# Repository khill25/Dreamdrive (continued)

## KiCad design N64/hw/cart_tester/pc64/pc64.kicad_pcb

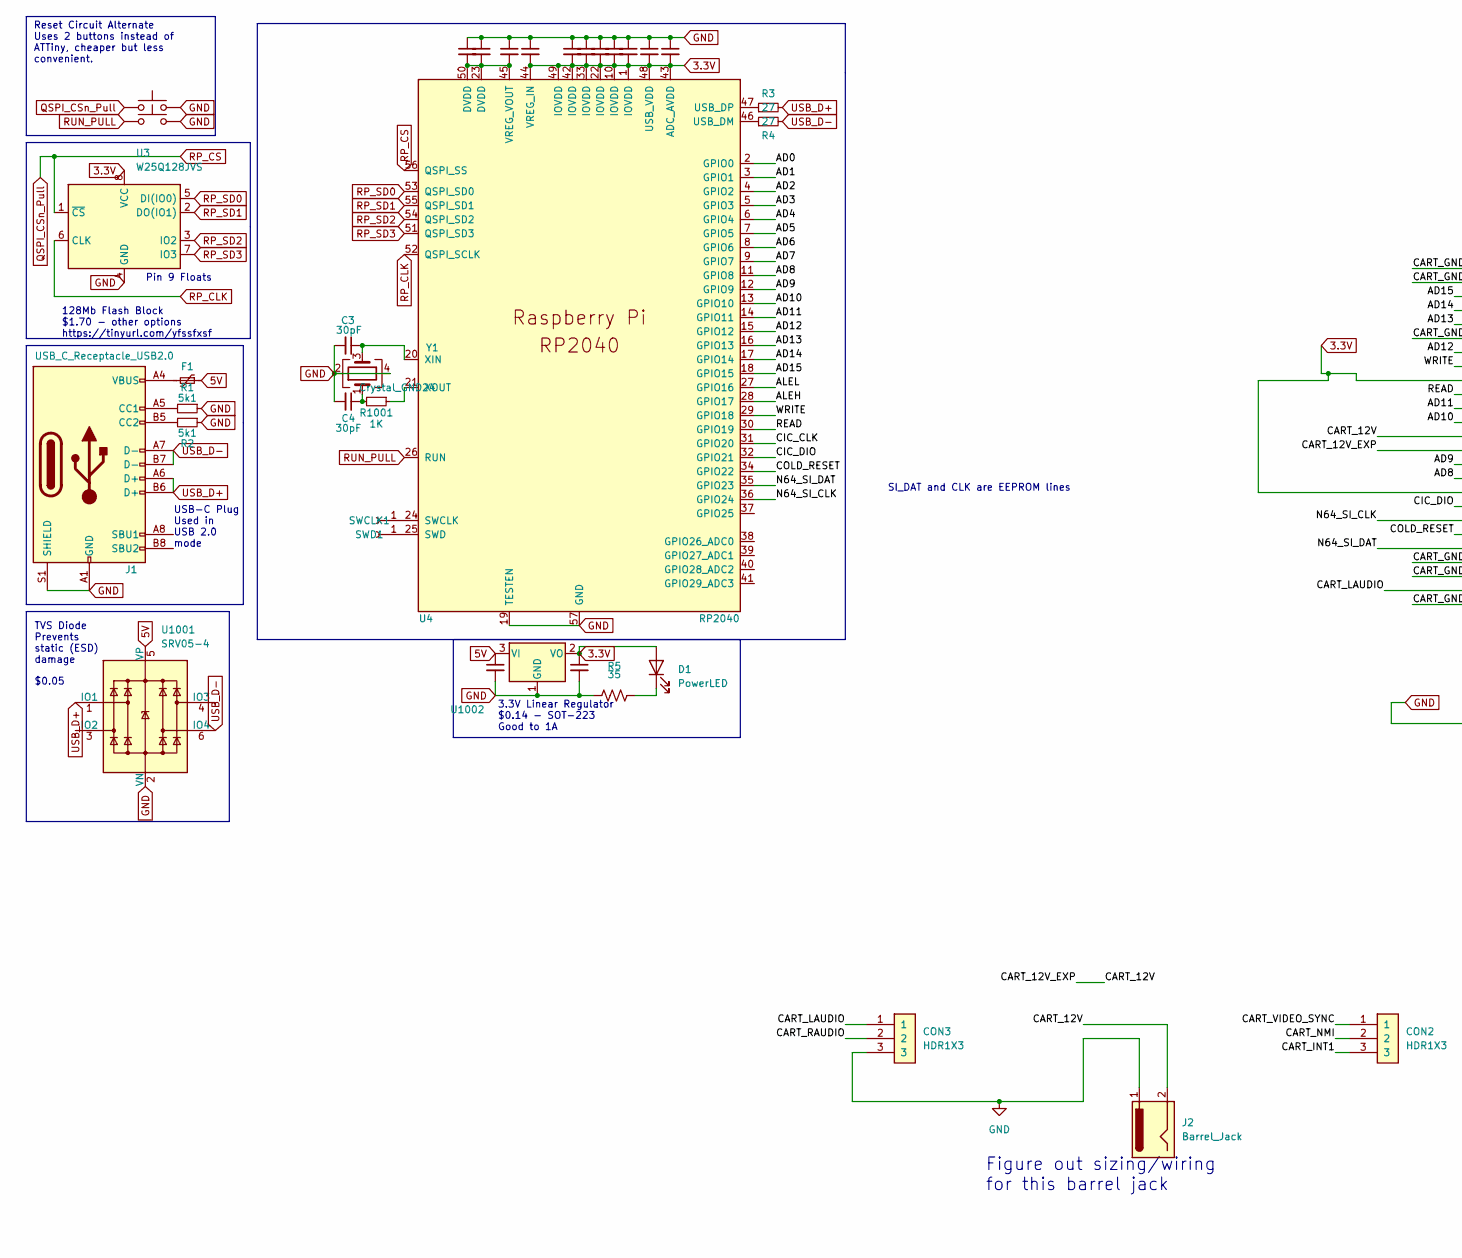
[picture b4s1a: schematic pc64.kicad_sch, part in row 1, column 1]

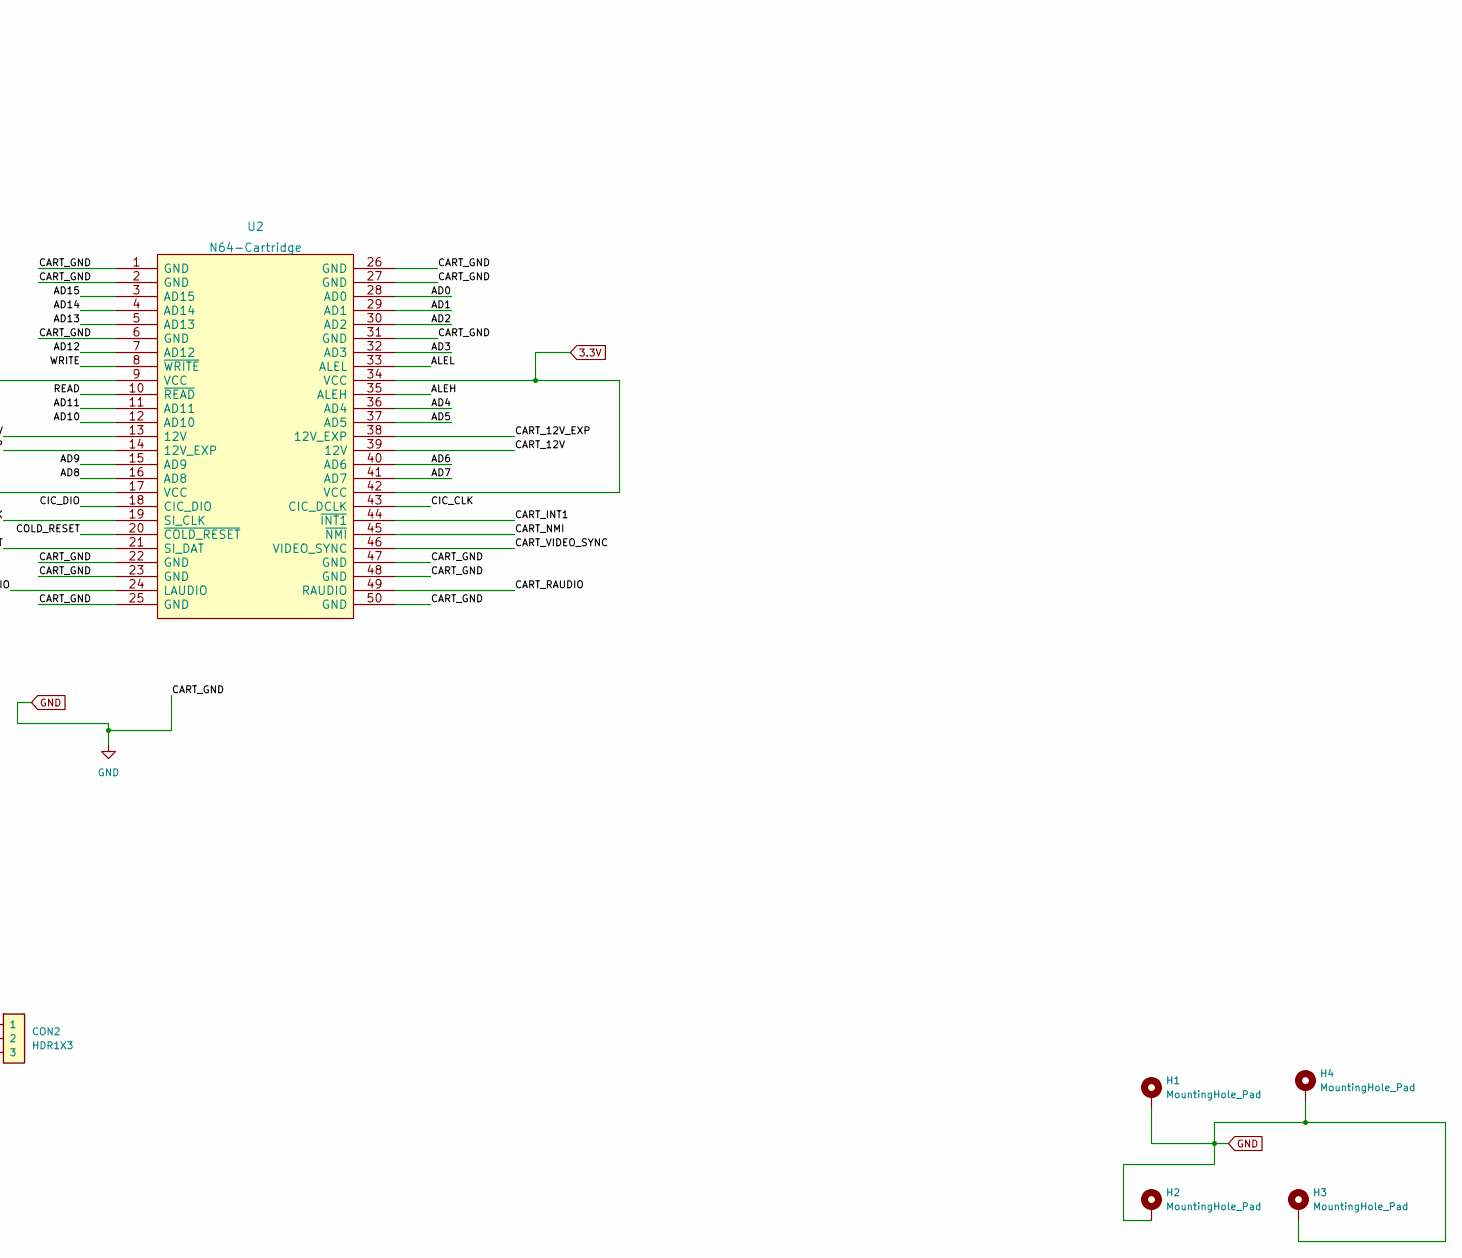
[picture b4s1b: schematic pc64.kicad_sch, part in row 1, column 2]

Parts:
C3, C4: 30pF; C_0402_1005Metric; LCSC C107004
C5, C6, C9, C10, C11, C13, C14, C15, C16: 100nF; C_0402_1005Metric; LCSC C1525
C7, C8, C1001, C1002: 1uF; C_0402_1005Metric; LCSC C52923
CON2, CON3: HDR1X3; PinSocket_1x03_P2.54mm_Vertical; Digikey 732-5316-ND
D1: PowerLED; LED_0402_1005Metric; LCSC C130724
F1: 1.1A; Fuse_1206_3216Metric; LCSC C2760273
H1, H2, H3, H4: MountingHole_Pad; MountingHole_2.2mm_M2_ISO7380_Pad_TopBottom
J1: USB_C_Receptacle_USB2.0; USB_C_Receptacle_HRO_TYPE-C-31-M-12; LCSC C165948
J2: Barrel_Jack; BarrelJack_CUI_PJ-036AH-SMT_Horizontal
R1, R2: 5k1; R_0402_1005Metric; LCSC C25905
R3, R4: 27; R_0402_1005Metric; LCSC C25100
R5: 35; R_0402_1005Metric
R1001: 1K; R_0402_1005Metric; LCSC C11702
RP_SW1, RP_SW2: SW_Push; SW_SPST_TL3342; LCSC C318884
SWCLK1: Conn_01x01_Female; TestPoint_Pad_D1.0mm
SWD1: Conn_01x01_Female; TestPoint_Pad_D1.0mm
U2: N64-Cartridge; N64-CONN
U3: W25Q128JVS; SOIC-8_5.23x5.23mm_P1.27mm; LCSC C97521
U4: RP2040; QFN-56-1EP_7x7mm_P0.4mm_EP3.2x3.2mm; LCSC C2040
U1001: SRV05-4; SOT-23-6; LCSC C3021103
U1002: AMS1117-3.3; SOT-223; LCSC C6186
Y1: Crystal_GND24; Crystal_SMD_3225-4Pin_3.2x2.5mm; LCSC C9002

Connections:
3.3V: C8.2, C9.2, C10.2, C11.2, C13.2, C14.2, C15.2, C16.2, C1002.1, D1.2 (A), U2.9 (VCC), U2.17 (VCC), U2.34 (VCC), U2.42 (VCC), U3.8 (VCC), U4.1 (IOVDD), U4.10 (IOVDD), U4.22 (IOVDD), U4.33 (IOVDD), U4.42 (IOVDD), U4.43 (ADC_AVDD), U4.44 (VREG_IN), U4.48 (USB_VDD), U4.49 (IOVDD), U1002.2 (VO)
5V: C1001.1, F1.1, U1001.5 (VP), U1002.3 (VI)
/AD0: U2.28 (AD0), U4.2 (GPIO0)
/AD1: U2.29 (AD1), U4.3 (GPIO1)
/AD2: U2.30 (AD2), U4.4 (GPIO2)
/AD3: U2.32 (AD3), U4.5 (GPIO3)
/AD4: U2.36 (AD4), U4.6 (GPIO4)
/AD5: U2.37 (AD5), U4.7 (GPIO5)
/AD6: U2.40 (AD6), U4.8 (GPIO6)
/AD7: U2.41 (AD7), U4.9 (GPIO7)
/AD8: U2.16 (AD8), U4.11 (GPIO8)
/AD9: U2.15 (AD9), U4.12 (GPIO9)
/AD10: U2.12 (AD10), U4.13 (GPIO10)
/AD11: U2.11 (AD11), U4.14 (GPIO11)
/AD12: U2.7 (AD12), U4.15 (GPIO12)
/AD13: U2.5 (AD13), U4.16 (GPIO13)
/AD14: U2.4 (AD14), U4.17 (GPIO14)
/AD15: U2.3 (AD15), U4.18 (GPIO15)
/ALEH: U2.35 (ALEH), U4.28 (GPIO17)
/ALEL: U2.33 (ALEL), U4.27 (GPIO16)
/CART_12V: J2.2, U2.13 (12V), U2.14 (12V_EXP), U2.38 (12V_EXP), U2.39 (12V)
/CART_INT1: CON2.3, U2.44 (~INT1)
/CART_LAUDIO: CON3.1, U2.24 (LAUDIO)
/CART_NMI: CON2.2, U2.45 (~NMI)
/CART_RAUDIO: CON3.2, U2.49 (RAUDIO)
/CART_VIDEO_SYNC: CON2.1, U2.46 (VIDEO_SYNC)
/CIC_CLK: U2.43 (CIC_DCLK), U4.31 (GPIO20)
/CIC_DIO: U2.18 (CIC_DIO), U4.32 (GPIO21)
/COLD_RESET: U2.20 (~COLD_RESET), U4.34 (GPIO22)
/N64_SI_CLK: U2.19 (SI_CLK), U4.36 (GPIO24)
/N64_SI_DAT: U2.21 (SI_DAT), U4.35 (GPIO23)
/READ: U2.10 (~READ), U4.30 (GPIO19)
/WRITE: U2.8 (~WRITE), U4.29 (GPIO18)
unnamed: C4.1, R1001.2, Y1.1
unnamed: D1.1 (K), R5.2
unnamed: F1.2, J1.A4 (VBUS), J1.A9 (VBUS), J1.B4 (VBUS), J1.B9 (VBUS)
unnamed: J1.A5 (CC1), R1.2
unnamed: J1.B5 (CC2), R2.2
unnamed: SWD1.1, U4.25 (SWD)
unnamed: R4.1, U4.46 (USB_DM)
unnamed: R3.1, U4.47 (USB_DP)
unnamed: C5.2, C6.2, C7.2, U4.23 (DVDD), U4.45 (VREG_VOUT), U4.50 (DVDD)
unnamed: C3.1, U4.20 (XIN), Y1.3
unnamed: R1001.1, U4.21 (XOUT)
QSPI_CSn_Pull: RP_SW1.1, U3.1 (~CS), U4.56 (QSPI_SS)
RP_CLK: U3.6 (CLK), U4.52 (QSPI_SCLK)
RP_SD0: U3.5 (DI(IO0)), U4.53 (QSPI_SD0)
RP_SD1: U3.2 (DO(IO1)), U4.55 (QSPI_SD1)
RP_SD2: U3.3 (IO2), U4.54 (QSPI_SD2)
RP_SD3: U3.7 (IO3), U4.51 (QSPI_SD3)
RUN_PULL: RP_SW2.1, U4.26 (RUN)
USB_D+: J1.A6 (D+), J1.B6 (D+), R3.2, U1001.1 (IO1)
USB_D-: J1.A7 (D-), J1.B7 (D-), R4.2, U1001.6 (IO4)

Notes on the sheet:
3.3V Linear Regulator $0.14 - SOT-223 Good to 1A
USB-C Plug Used in USB 2.0 mode
Pin 9 Floats
Reset Circuit Alternate Uses 2 buttons instead of ATTiny, cheaper but less convenient.
$0.05
Figure out sizing/wiring for this barrel jack
TVS Diode Prevents static (ESD) damage
128Mb Flash Block $1.70 - other options https://tinyurl.com/yfssfxsf
SI_DAT and CLK are EEPROM lines

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
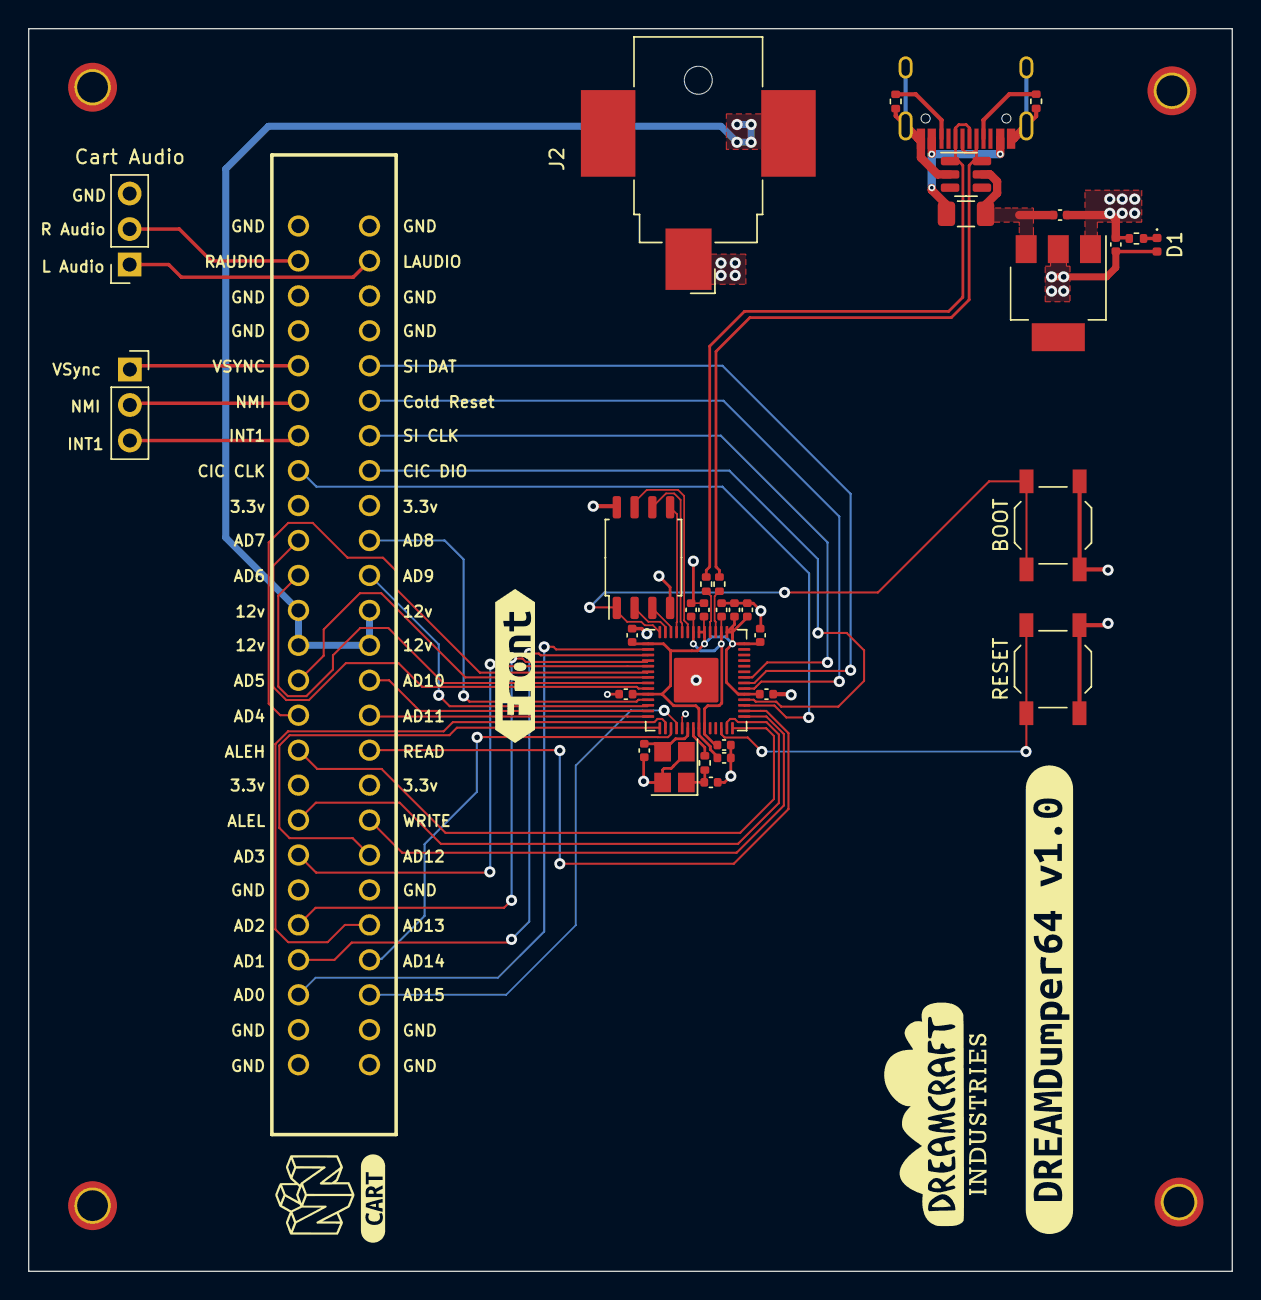
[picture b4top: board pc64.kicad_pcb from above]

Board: 4 copper layers, 86.1 x 88.9 mm, 43 parts (0 on the bottom side), 53 nets.

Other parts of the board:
Logo: LOGO
kibuzzard-665BAD6D: G***; kibuzzard-665BAD6D
kibuzzard-665BADED: G***; kibuzzard-665BADED
kibuzzard-665BAE91: G***; kibuzzard-665BAE91

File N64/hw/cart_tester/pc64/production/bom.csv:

Designator,Footprint,Quantity,Value,LCSC Part #
"C10, C11, C13, C14, C15, C16, C5, C6, C9",0402,9,100nF,C1525
"C1001, C1002, C7, C8",0402,4,1uF,C52923
"C3, C4",0402,2,30pF,C107004
CON2,PinSocket_1x03_P2.54mm_Vertical,1,HDR1X3,C146243
CON3,PinSocket_1x03_P2.54mm_Vertical,1,HDR1X3,
D1,0402,1,PowerLED,C130724
F1,1206,1,1.1A,C2760273
"H1, H2, H3, H4",MountingHole_2.2mm_M2_ISO7380_Pad_TopBottom,4,MountingHole_Pad,
J1,HRO-TYPE-C-31-M-12_LCSC,1,USB_C_Receptacle_USB2.0,C165948
J2,BarrelJack_CUI_PJ-036AH-SMT_Horizontal,1,Barrel_Jack,
"R1, R2",0402,2,5k1,C25905
R1001,0402,1,1K,C11702
"R3, R4",0402,2,27,C25100
R5,0402,1,35,
"RP_SW1, RP_SW2",SW_SPST_TL3342,2,SW_Push,C318884
U1001,SOT-23-6,1,SRV05-4,C3021103
U1002,SOT-223,1,AMS1117-3.3,C6186
U3,SOIC-8_5.23x5.23mm_P1.27mm,1,W25Q128JVS,C97521
U4,RP2040-QFN-56,1,RP2040,C2040
Y1,Crystal_SMD_3225-4Pin_3.2x2.5mm,1,Crystal_GND24,C9002

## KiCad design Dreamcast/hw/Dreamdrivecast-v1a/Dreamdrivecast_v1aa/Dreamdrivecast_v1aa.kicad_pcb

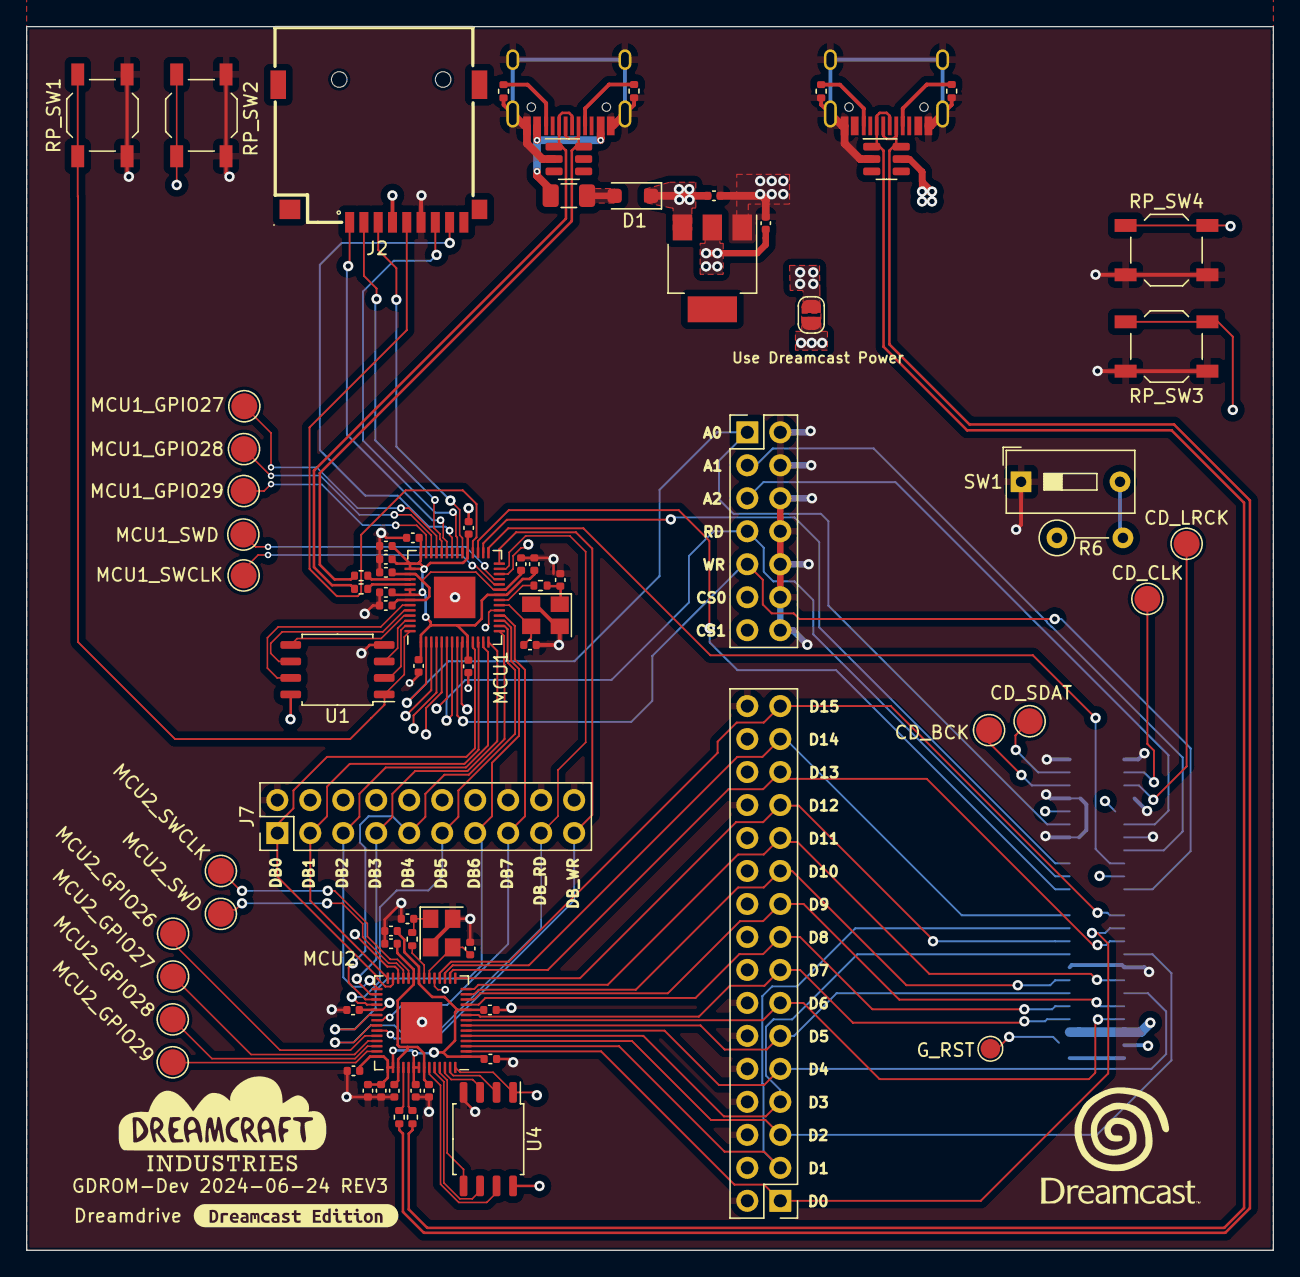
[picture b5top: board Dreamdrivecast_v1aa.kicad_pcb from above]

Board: 4 copper layers, 96.0 x 94.2 mm, 81 parts (1 on the bottom side), 99 nets.

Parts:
C1, C2, C5, C6, C7, C8, C9, C10, C11, C16, C17, C20, C21, C22, C23, C24, C25, C26: 100nF; C_0402_1005Metric
C3, C4, C14, C15, C18, C19: 1uF; C_0402_1005Metric
C12, C13, C27, C28: 30pF; C_0402_1005Metric
CD_BCK: TestPoint_Pad_D2.0mm
CD_CLK: TestPoint_Pad_D2.0mm
CD_LRCK: TestPoint_Pad_D2.0mm
CD_SDAT: TestPoint_Pad_D2.0mm
CN1: Molex_52602_0579
D1: D_Schottky; D_SOD-123F
DREAMCRAFT_LOGO: LOGO
F1: 1.1A; Fuse_1206_3216Metric
G_RST: TestPoint_Pad_D1.5mm
J1, J5: USB_C_Receptacle_USB2.0; HRO-TYPE-C-31-M-12_LCSC
J2: Micro_SD_Card; TF-SMD_TF-PUSH
J4: Dreamcast Data; PinHeader_2x16_P2.54mm_Vertical
J6: Dreamcast Control Lines; PinHeader_2x07_P2.54mm_Vertical
J7: MCU Databus; PinHeader_2x10_P2.54mm_Vertical
MCU1, MCU2: RP2040; QFN-56-1EP_7x7mm_P0.4mm_EP3.2x3.2mm
MCU1_GPIO27, MCU1_GPIO28, MCU1_GPIO29, MCU1_SWCLK, MCU1_SWD, MCU2_GPIO26, MCU2_GPIO27, MCU2_GPIO28, MCU2_GPIO29, MCU2_SWCLK, MCU2_SWD: TestPoint_Pad_D2.0mm
R1, R2, R7, R8: 27; R_0402_1005Metric
R3, R9: 1K; R_0402_1005Metric
R4, R5, R10, R11: 5k1; R_0402_1005Metric
R6: R; R_Axial_DIN0207_L6.3mm_D2.5mm_P5.08mm_Vertical
RP_SW1, RP_SW2, RP_SW3, RP_SW4: SW_Push; SW_SPST_TL3342
SW1: Lid; SW_DIP_SPSTx01_Slide_9.78x4.72mm_W7.62mm_P2.54mm
U1, U4: W25Q128JVS; SOIC-8_5.23x5.23mm_P1.27mm
U2: AMS1117-3.3; SOT-223
U3, U6: SRV05-4; SOT-23-6
Use Dreamcast Power: SolderJumper-2_P1.3mm_Open_RoundedPad1.0x1.5mm
Y1, Y2: Crystal_GND24; Crystal_SMD_3225-4Pin_3.2x2.5mm
kibuzzard-63F149CE: DDR_DREAMCAST; kibuzzard-63F149CE

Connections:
3.3V: C4.2, C5.2, C6.2, C7.2, C8.2, C9.2, C10.2, C11.2, C15.1, C19.2, C20.2, C21.2, C22.2, C23.2, C24.2, C25.2, C26.2, J2.4 (VDD), MCU1.1 (IOVDD), MCU1.10 (IOVDD), MCU1.22 (IOVDD), MCU1.33 (IOVDD), MCU1.42 (IOVDD), MCU1.43 (ADC_AVDD), MCU1.44 (VREG_IN), MCU1.48 (USB_VDD), MCU1.49 (IOVDD), MCU2.1 (IOVDD), MCU2.10 (IOVDD), MCU2.22 (IOVDD), MCU2.33 (IOVDD), MCU2.42 (IOVDD), MCU2.43 (ADC_AVDD), MCU2.44 (VREG_IN), MCU2.48 (USB_VDD), MCU2.49 (IOVDD), U1.8 (VCC), U2.2 (VO), U4.8 (VCC)
5V: C14.1, D1.1 (K), U2.3 (VI), U3.5 (VP), U6.5 (VP), Use Dreamcast Power.2
/A0: CN1.A19, J6.1, MCU1.2 (GPIO0)
/A1: CN1.B17, J6.2, MCU1.3 (GPIO1)
/A2: CN1.B19, J6.3, MCU1.4 (GPIO2)
/CD_BCK: CD_BCK.1, CN1.A22
/CD_CLK: CD_CLK.1, CN1.B23
/CD_LRCK: CD_LRCK.1, CN1.B22
/CD_SDAT: CD_SDAT.1, CN1.A23
/CS0: CN1.A20, MCU1.5 (GPIO3)
/CS1: CN1.B20, MCU1.6 (GPIO4)
/D0: CN1.B11, J4.1, MCU2.2 (GPIO0)
/D1: CN1.A11, J4.2, MCU2.3 (GPIO1)
/D2: CN1.B9, J4.3, MCU2.4 (GPIO2)
/D3: CN1.A9, J4.4, MCU2.5 (GPIO3)
/D4: CN1.B6, J4.5, MCU2.6 (GPIO4)
/D5: CN1.A6, J4.6, MCU2.7 (GPIO5)
/D6: CN1.B4, J4.7, MCU2.8 (GPIO6)
/D7: CN1.A4, J4.8, MCU2.9 (GPIO7)
/D8: CN1.A5, J4.9, MCU2.11 (GPIO8)
/D9: CN1.B5, J4.10, MCU2.12 (GPIO9)
/D10: CN1.A7, J4.11, MCU2.13 (GPIO10)
/D11: CN1.B7, J4.12, MCU2.14 (GPIO11)
/D12: CN1.A10, J4.13, MCU2.15 (GPIO12)
/D13: CN1.B10, J4.14, MCU2.16 (GPIO13)
/D14: CN1.A12, J4.15, MCU2.17 (GPIO14)
/D15: CN1.B12, J4.16, MCU2.18 (GPIO15)
/DATABUS_D0: J7.1, MCU1.11 (GPIO8), MCU2.27 (GPIO16)
/DATABUS_D1: J7.2, MCU1.12 (GPIO9), MCU2.28 (GPIO17)
/DATABUS_D2: J7.3, MCU1.13 (GPIO10), MCU2.29 (GPIO18)
/DATABUS_D3: J7.4, MCU1.14 (GPIO11), MCU2.30 (GPIO19)
/DATABUS_D4: J7.5, MCU1.15 (GPIO12), MCU2.31 (GPIO20)
/DATABUS_D5: J7.6, MCU1.16 (GPIO13), MCU2.32 (GPIO21)
/DATABUS_D6: J7.7, MCU1.17 (GPIO14), MCU2.34 (GPIO22)
/DATABUS_D7: J7.8, MCU1.18 (GPIO15), MCU2.35 (GPIO23)
/DATABUS_SIGNAL_READ: J7.9, MCU1.27 (GPIO16), MCU2.36 (GPIO24)
/DATABUS_SIGNAL_WRITE: J7.10, MCU1.28 (GPIO17), MCU2.37 (GPIO25)
/DMACK: CN1.A16, MCU1.30 (GPIO19)
/DMARQ: CN1.A14, MCU1.31 (GPIO20)
/DOPEN: CN1.B2, R6.2, SW1.2 (B)
/G_RST: CN1.A2, G_RST.1
/INTRQ: CN1.B16, MCU1.29 (GPIO18)
/IORDY: CN1.B15, MCU1.9 (GPIO7)
/MCU1_GPIO27: MCU1.39 (GPIO27_ADC1), MCU1_GPIO27.1
/MCU1_GPIO28: MCU1.40 (GPIO28_ADC2), MCU1_GPIO28.1
/MCU1_GPIO29: MCU1.41 (GPIO29_ADC3), MCU1_GPIO29.1
/MCU2_GPIO26: MCU2.38 (GPIO26_ADC0), MCU2_GPIO26.1
/MCU2_GPIO27: MCU2.39 (GPIO27_ADC1), MCU2_GPIO27.1
/MCU2_GPIO28: MCU2.40 (GPIO28_ADC2), MCU2_GPIO28.1
/MCU2_GPIO29: MCU2.41 (GPIO29_ADC3), MCU2_GPIO29.1
/RD: CN1.A15, J6.4, MCU1.7 (GPIO5)
/SD_CLK: J2.5 (CLK), MCU1.32 (GPIO21)
/SD_CMD: J2.3 (CMD), MCU1.34 (GPIO22)
/SD_DAT0: J2.7 (DAT0), MCU1.35 (GPIO23)
/SD_DAT1: J2.8 (DAT1), MCU1.36 (GPIO24)
/SD_DAT2: J2.1 (DAT2), MCU1.37 (GPIO25)
/SD_DAT3: J2.2 (DAT3/CD), MCU1.38 (GPIO26_ADC0)
/WR: CN1.B14, J6.5, MCU1.8 (GPIO6)
Dreamcast_3v3: CN1.A1, CN1.B1
Dreamcast_5V: CN1.A3, CN1.B3, Use Dreamcast Power.1
Dreamcast_12V: CN1.A25, CN1.B25
GND: C1.1, C2.1, C3.1, C4.1, C5.1, C6.1, C7.1, C8.1, C9.1, C10.1, C11.1, C12.2, C13.2, C14.2, C15.2, C16.1, C17.1, C18.1, C19.1, C20.1, C21.1, C22.1, C23.1, C24.1, C25.1, C26.1, C27.2, C28.2, CN1.A8, CN1.A13, CN1.A18, CN1.A21, CN1.A24, CN1.B8, CN1.B13, CN1.B18, CN1.B21, CN1.B24, J1.A1 (GND), J1.A12 (GND), J1.B1 (GND), J1.B12 (GND), J1.S1 (SHIELD), J2.6 (VSS), J4.17, J4.18, J4.19, J4.20, J4.21, J4.22, J4.23, J4.24, J4.25, J4.26, J4.27, J4.28, J4.29, J4.30, J4.31, J4.32, J5.A1 (GND), J5.A12 (GND), J5.B1 (GND), J5.B12 (GND), J5.S1 (SHIELD), J6.8, J6.9, J6.10, J6.11, J6.12, J6.13, J6.14, J7.11, J7.12, J7.13, J7.14, J7.15, J7.16, J7.17, J7.18, J7.19, J7.20, MCU1.19 (TESTEN), MCU1.57 (GND), MCU2.19 (TESTEN), MCU2.57 (GND), R4.1, R5.1, R10.1, R11.1, RP_SW1.2, RP_SW2.2, RP_SW3.2, RP_SW4.2, SW1.1 (A), U1.4 (GND), U2.1 (GND), U3.2 (VN), U4.4 (GND), U6.2 (VN), Y1.2, Y1.4, Y2.2, Y2.4
unnamed: C13.1, R3.2, Y1.1
unnamed: C28.1, R9.2, Y2.1
unnamed: J1.A5 (CC1), J5.A5 (CC1), R5.2, R11.2
unnamed: J1.B5 (CC2), J5.B5 (CC2), R4.2, R10.2
unnamed: MCU1.24 (SWCLK), MCU1_SWCLK.1
unnamed: MCU1.25 (SWD), MCU1_SWD.1
unnamed: MCU1.46 (USB_DM), R2.1
unnamed: MCU1.47 (USB_DP), R1.1
unnamed: C1.2, C2.2, C3.2, MCU1.23 (DVDD), MCU1.45 (VREG_VOUT), MCU1.50 (DVDD)
unnamed: C12.1, MCU1.20 (XIN), Y1.3
unnamed: MCU1.21 (XOUT), R3.1
unnamed: MCU2.24 (SWCLK), MCU2_SWCLK.1
unnamed: MCU2.25 (SWD), MCU2_SWD.1
unnamed: MCU2.46 (USB_DM), R8.1
unnamed: MCU2.47 (USB_DP), R7.1
unnamed: C16.2, C17.2, C18.2, MCU2.23 (DVDD), MCU2.45 (VREG_VOUT), MCU2.50 (DVDD)
unnamed: C27.1, MCU2.20 (XIN), Y2.3
unnamed: MCU2.21 (XOUT), R9.1
RP1_CLK: MCU1.52 (QSPI_SCLK), U1.6 (CLK)
RP1_CS: MCU1.56 (QSPI_SS), RP_SW1.1, U1.1 (~CS)
RP1_RUN_PULL: MCU1.26 (RUN), RP_SW2.1
RP1_SD0: MCU1.53 (QSPI_SD0), U1.5 (DI(IO0))
RP1_SD1: MCU1.55 (QSPI_SD1), U1.2 (DO(IO1))
RP1_SD2: MCU1.54 (QSPI_SD2), U1.3 (IO2)
RP1_SD3: MCU1.51 (QSPI_SD3), U1.7 (IO3)
RP1_USB_D+: J1.A6 (D+), J1.B6 (D+), R1.2, U3.1 (IO1)
RP1_USB_D-: J1.A7 (D-), J1.B7 (D-), R2.2, U3.6 (IO4)
RP2_CLK: MCU2.52 (QSPI_SCLK), U4.6 (CLK)
RP2_CS: MCU2.56 (QSPI_SS), RP_SW3.1, U4.1 (~CS)
RP2_RUN_PULL: MCU2.26 (RUN), RP_SW4.1
RP2_SD0: MCU2.53 (QSPI_SD0), U4.5 (DI(IO0))
RP2_SD1: MCU2.55 (QSPI_SD1), U4.2 (DO(IO1))
RP2_SD2: MCU2.54 (QSPI_SD2), U4.3 (IO2)
RP2_SD3: MCU2.51 (QSPI_SD3), U4.7 (IO3)
RP2_USB_D+: J5.A6 (D+), J5.B6 (D+), R7.2, U6.1 (IO1)
RP2_USB_D-: J5.A7 (D-), J5.B7 (D-), R8.2, U6.6 (IO4)
VBUS: D1.2 (A), F1.1, F1.2, J1.A4 (VBUS), J1.A9 (VBUS), J1.B4 (VBUS), J1.B9 (VBUS), J5.A4 (VBUS), J5.A9 (VBUS), J5.B4 (VBUS), J5.B9 (VBUS)
